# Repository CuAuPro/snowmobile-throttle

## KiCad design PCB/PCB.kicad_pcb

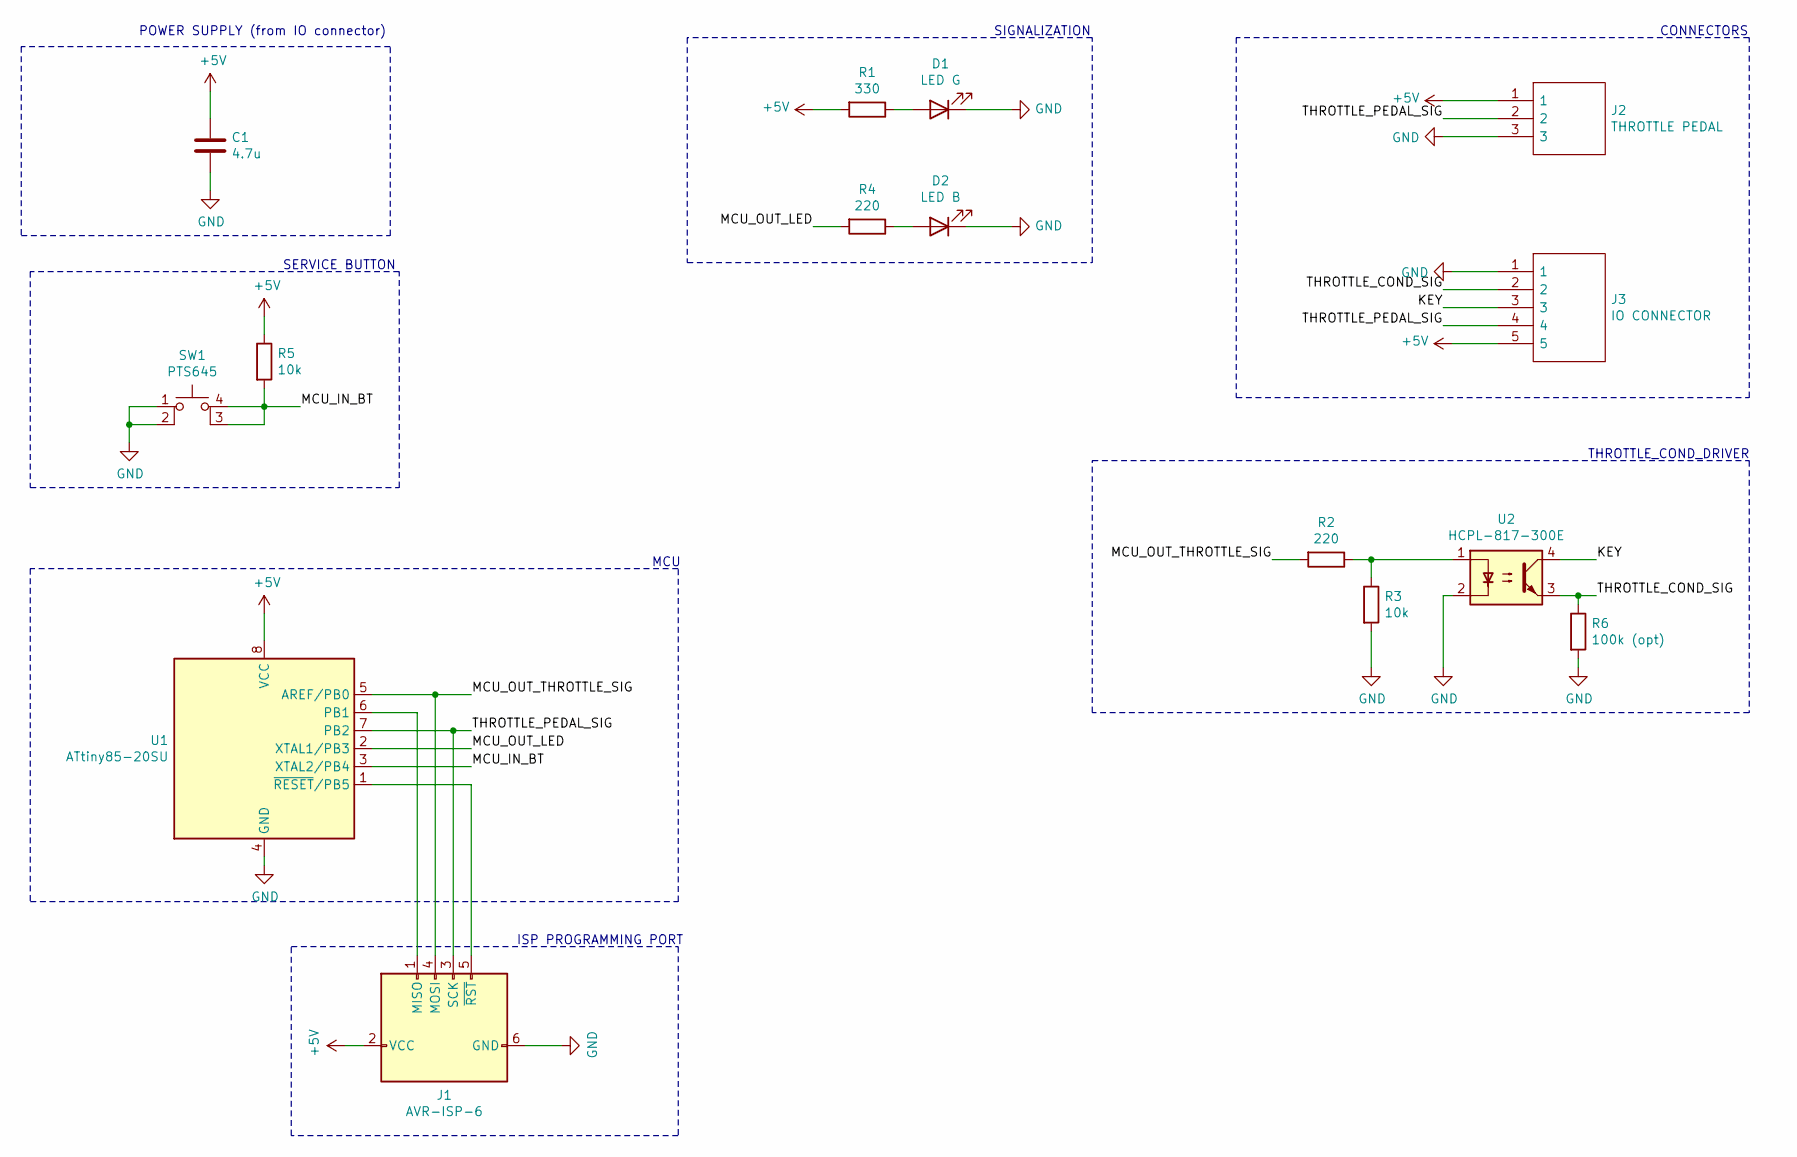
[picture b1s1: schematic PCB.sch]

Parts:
C1: 4.7u; C_0805_2012Metric_Pad1.18x1.45mm_HandSolder
D1: LED G; LED_0805_2012Metric_Pad1.15x1.40mm_HandSolder
D2: LED B; LED_0805_2012Metric_Pad1.15x1.40mm_HandSolder
J1: AVR-ISP-6; IDC-Header_2x03_P2.54mm_Vertical
J2: THROTTLE PEDAL; SHDR3W60P0X250_1X3_1000X640X880P; Manufacturer_Part_Number B03B-XASK-1(LF)(SN)
J3: IO CONNECTOR; RHDR5W60P0X250_1X5_1500X640X880P; Manufacturer_Part_Number B05B-XASK-1(LF)(SN)
R1: 330; R_0805_2012Metric_Pad1.20x1.40mm_HandSolder
R2, R4: 220; R_0805_2012Metric_Pad1.20x1.40mm_HandSolder
R3, R5: 10k; R_0805_2012Metric_Pad1.20x1.40mm_HandSolder
R6: 100k (opt); R_0805_2012Metric_Pad1.20x1.40mm_HandSolder
SW1: PTS645; PTS645(SMT)
U1: ATtiny85-20SU; SOIJ-8_5.3x5.3mm_P1.27mm
U2: HCPL-817-300E; SOP254P1016X460-4N

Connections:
+5V: C1.1, J1.2 (VCC), J2.1, J3.5, R1.2, R5.1, U1.8 (VCC)
/KEY: J3.3, U2.4
/MCU_IN_BT: R5.2, SW1.3 (K), SW1.4 (A), U1.3 (XTAL2/PB4)
/MCU_OUT_LED: R4.2, U1.2 (XTAL1/PB3)
/MCU_OUT_THROTTLE_SIG: J1.4 (MOSI), R2.2, U1.5 (AREF/PB0)
/THROTTLE_COND_SIG: J3.2, R6.1, U2.3
/THROTTLE_PEDAL_SIG: J1.3 (SCK), J2.2, J3.4, U1.7 (PB2)
GND: C1.2, D1.1 (K), D2.1 (K), J1.6 (GND), J2.3, J3.1, R3.2, R6.2, SW1.1, SW1.2, U1.4 (GND), U2.2
unnamed: D1.2 (A), R1.1
unnamed: D2.2 (A), R4.1
unnamed: J1.1 (MISO), U1.6 (PB1)
unnamed: J1.5 (~RST), U1.1 (~RESET~/PB5)
unnamed: R2.1, R3.1, U2.1

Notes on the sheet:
CONNECTORS
THROTTLE_COND_DRIVER
SIGNALIZATION
MCU
ISP PROGRAMMING PORT
SERVICE BUTTON
POWER SUPPLY (from IO connector)

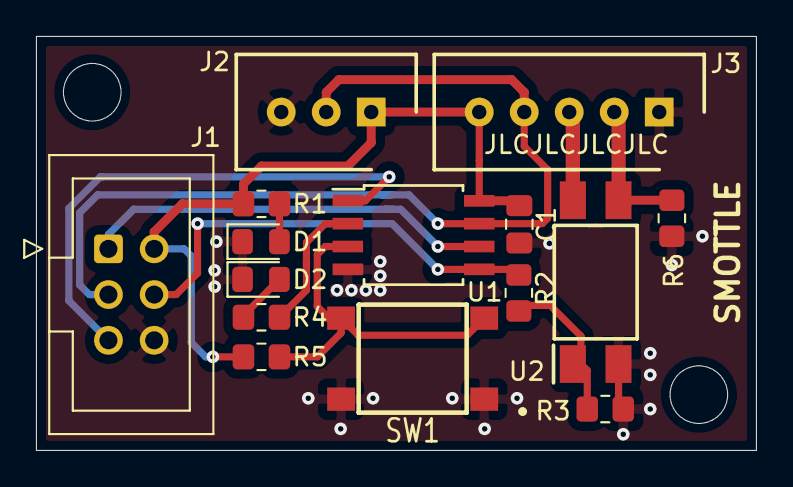
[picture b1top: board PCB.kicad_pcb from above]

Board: 2 copper layers, 40.0 x 23.0 mm, 17 parts (0 on the bottom side), 13 nets.

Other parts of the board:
MH1, MH2: MountingHole_3.2mm_M3_DIN965

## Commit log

2022-07-27 First working development version on Arduino Uno and finalized PCB.
2022-09-17 Adaptation changes.
